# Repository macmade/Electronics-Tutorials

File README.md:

Electronics-Tutorials
=====================

### About

Various electronics test projects.

### Software

Schemas and PCB layouts are created with KiCad:  
http://www.kicad-pcb.org

#### Footprints Library

This project requires the [XS-Labs KiCad Library](https://github.com/macmade/XS-KiCad-Library) to be installed in KiCad.

### Projects

  - [Astable Multivibrator](#1)
  - [SR Latch](#2)
  - [NPN Logic Gates](#3)

Astable Multivibrator
---------------------

### Bill Of Materials

| Manufacturer            | Part No.             | Details                                                                  | Quantity |
|-------------------------|----------------------|--------------------------------------------------------------------------|----------|
| ON Semiconductor        | [BC547BTF]           | Bipolar Transistors - BJT NPN 45V 100mA HFE/450                          | 2        |
| Vishay                  | [MAL214258109E3]     | Aluminium Electrolytic Capacitors - Radial Leaded 10uF 63V 20%           | 2        |
| VCC                     | [4302H1-12V]         | Standard LEDs - Red - 12V                                                | 2        |
| Vishay                  | [CCF071K00JKE36]     | Metal Film Resistors 1/4watt 1Kohms 5%                                   | 2        |
| Vishay                  | [CCF07100KJKE36]     | Metal Film Resistors 1/4watt 100Kohms 5%                                 | 2        |
| Wurth Elektronik        | [691214110002]       | Fixed Terminal Blocks WR-TBL 300VAC 10A 2P Horizontal                    | 1        |

[BC547BTF]: https://www.mouser.ch/ProductDetail/512-BC547BTF
[MAL214258109E3]: https://www.mouser.ch/ProductDetail/594-MAL203858109E3
[4302H1-12V]: https://www.mouser.ch/ProductDetail/606-4302H1-12V
[CCF071K00JKE36]: https://www.mouser.ch/ProductDetail/71-CCF071K00JKE36
[CCF07100KJKE36]: https://www.mouser.ch/ProductDetail/71-CCF07100KJKE36
[691214110002]: https://www.mouser.ch/ProductDetail/710-691214110002

SR Latch
--------

### Bill Of Materials

| Manufacturer            | Part No.             | Details                                                                  | Quantity |
|-------------------------|----------------------|--------------------------------------------------------------------------|----------|
| ON Semiconductor        | [BC547BTF]           | Bipolar Transistors - BJT NPN 45V 100mA HFE/450                          | 4        |
| VCC                     | [4302H5-12V]         | Standard LEDs - Green - 12V                                              | 1        |
| VCC                     | [4302H1-12V]         | Standard LEDs - Red - 12V                                                | 1        |
| Vishay                  | [CCF07390RJKE36]     | Metal Film Resistors 1/4watt 390ohms 5%                                  | 2        |
| Vishay                  | [CCF071K00JKE36]     | Metal Film Resistors 1/4watt 1Kohms 5%                                   | 4        |
| Vishay                  | [CCF0710K0JKE36]     | Metal Film Resistors 1/4watt 10Kohms 5%                                  | 4        |
| Omron                   | [B3W-9010-R1R]       | Tactile Switches - Green                                                 | 1        |
| Omron                   | [B3W-9010-R1R]       | Tactile Switches - Red                                                   | 1        |
| Wurth Elektronik        | [691214110002]       | Fixed Terminal Blocks WR-TBL 300VAC 10A 2P Horizontal                    | 1        |

[BC547BTF]: https://www.mouser.ch/ProductDetail/512-BC547BTF
[4302H5-12V]: https://www.mouser.ch/ProductDetail/606-4302H5-12V
[4302H1-12V]: https://www.mouser.ch/ProductDetail/606-4302H1-12V
[CCF07390RJKE36]: https://www.mouser.ch/ProductDetail/71-CCF07390RJKE36
[CCF071K00JKE36]: https://www.mouser.ch/ProductDetail/71-CCF071K00JKE36
[CCF0710K0JKE36]: https://www.mouser.ch/ProductDetail/71-CCF0710K0JKE36
[B3W-9010-G1G]: https://www.mouser.ch/ProductDetail/653-B3W-9010-G1G
[B3W-9010-R1R]: https://www.mouser.ch/ProductDetail/653-B3W-9010-R1R
[691214110002]: https://www.mouser.ch/ProductDetail/710-691214110002

NPN Logic Gates
---------------

| Manufacturer            | Part No.             | Details                                                                  | Quantity |
|-------------------------|----------------------|--------------------------------------------------------------------------|----------|
| ON Semiconductor        | [BC547BTF]           | Bipolar Transistors - BJT NPN 45V 100mA HFE/450                          | 24       |
| VCC                     | [4302H5-12V]         | Standard LEDs - Green - 12V                                              | 6        |
| VCC                     | [4302H1-12V]         | Standard LEDs - Red - 12V                                                | 4        |
| Vishay                  | [CCF07390RJKE36]     | Metal Film Resistors 1/4watt 390ohms 5%                                  | 10       |
| Vishay                  | [CCF071K00JKE36]     | Metal Film Resistors 1/4watt 1Kohms 5%                                   | 14       |
| Vishay                  | [CCF0710K0JKE36]     | Metal Film Resistors 1/4watt 10Kohms 5%                                  | 24       |
| NKK Switches            | [M2012SA1W03]        | Toggle Switches ON-ON PC SPDT                                            | 2        |
| Wurth Elektronik        | [691214110002]       | Fixed Terminal Blocks WR-TBL 300VAC 10A 2P Horizontal                    | 1        |

[BC547BTF]: https://www.mouser.ch/ProductDetail/512-BC547BTF
[4302H5-12V]: https://www.mouser.ch/ProductDetail/606-4302H5-12V
[4302H1-12V]: https://www.mouser.ch/ProductDetail/606-4302H1-12V
[CCF07390RJKE36]: https://www.mouser.ch/ProductDetail/71-CCF07390RJKE36
[CCF071K00JKE36]: https://www.mouser.ch/ProductDetail/71-CCF071K00JKE36
[CCF0710K0JKE36]: https://www.mouser.ch/ProductDetail/71-CCF0710K0JKE36
[M2012SA1W03]: https://www.mouser.ch/ProductDetail/633-M2012A03
[691214110002]: https://www.mouser.ch/ProductDetail/710-691214110002

License
-------

All project files are released under the terms of the CERN Open Hardware License - CERN OHL v.1.2.

Repository Infos
----------------

    Owner:          Jean-David Gadina - XS-Labs
    Web:            www.xs-labs.com
    Blog:           www.noxeos.com
    Twitter:        @macmade
    GitHub:         github.com/macmade
    LinkedIn:       ch.linkedin.com/in/macmade/
    StackOverflow:  stackoverflow.com/users/182676/macmade

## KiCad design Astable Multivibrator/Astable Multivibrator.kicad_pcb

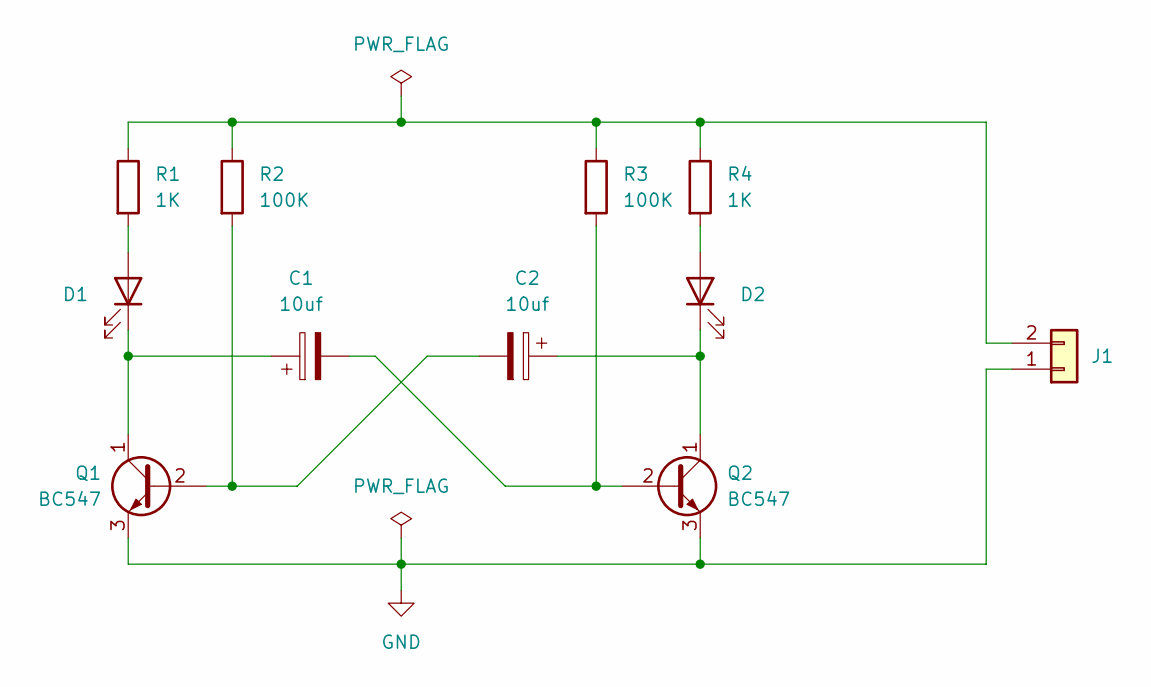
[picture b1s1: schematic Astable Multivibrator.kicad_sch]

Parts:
C1, C2: 10uf; Capacitor-Vishay-142-RHS-5x11x2mm
D1, D2: LED; LED-T1-34-5mm
J1: Conn_01x02; Connector-Wurth-Terminal-Block-2P-3.5mm-691214110002
Q1, Q2: BC547; Transistor-NPN-TO-92-Line-Spacing-Lead-Form
R1, R4: 1K; Resistor-Vishay-CCF07
R2, R3: 100K; Resistor-Vishay-CCF07

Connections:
GND: J1.1, Q1.3 (E), Q2.3 (E)
unnamed: D1.2 (A), R1.2
unnamed: C1.1, D1.1 (K), Q1.1 (C)
unnamed: D2.2 (A), R4.2
unnamed: C2.1, D2.1 (K), Q2.1 (C)
unnamed: J1.2, R1.1, R2.1, R3.1, R4.1
unnamed: C2.2, Q1.2 (B), R2.2
unnamed: C1.2, Q2.2 (B), R3.2

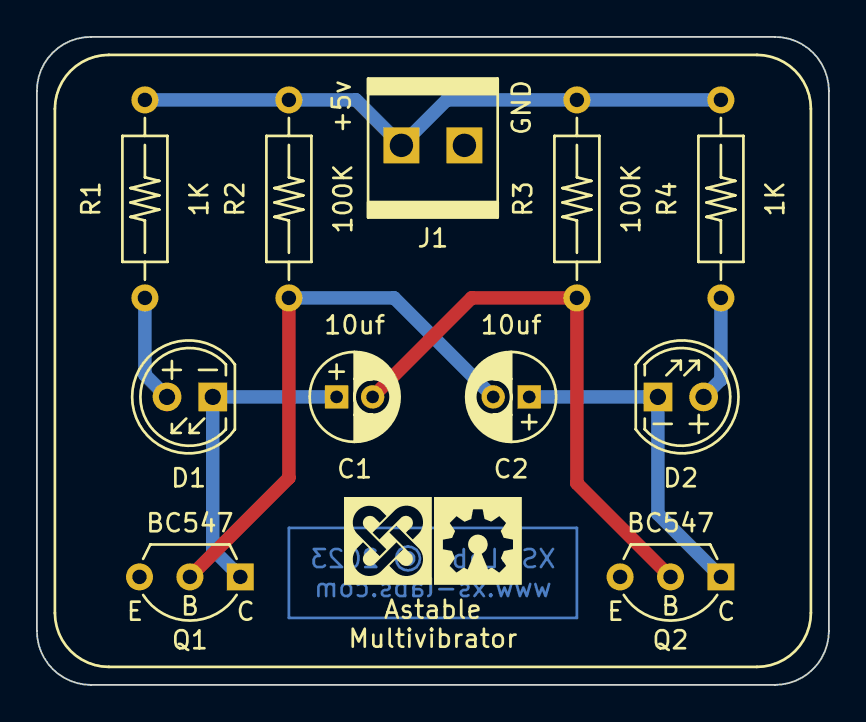
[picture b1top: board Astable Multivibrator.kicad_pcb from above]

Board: 2 copper layers, 44.0 x 36.0 mm, 11 parts (0 on the bottom side), 8 nets.

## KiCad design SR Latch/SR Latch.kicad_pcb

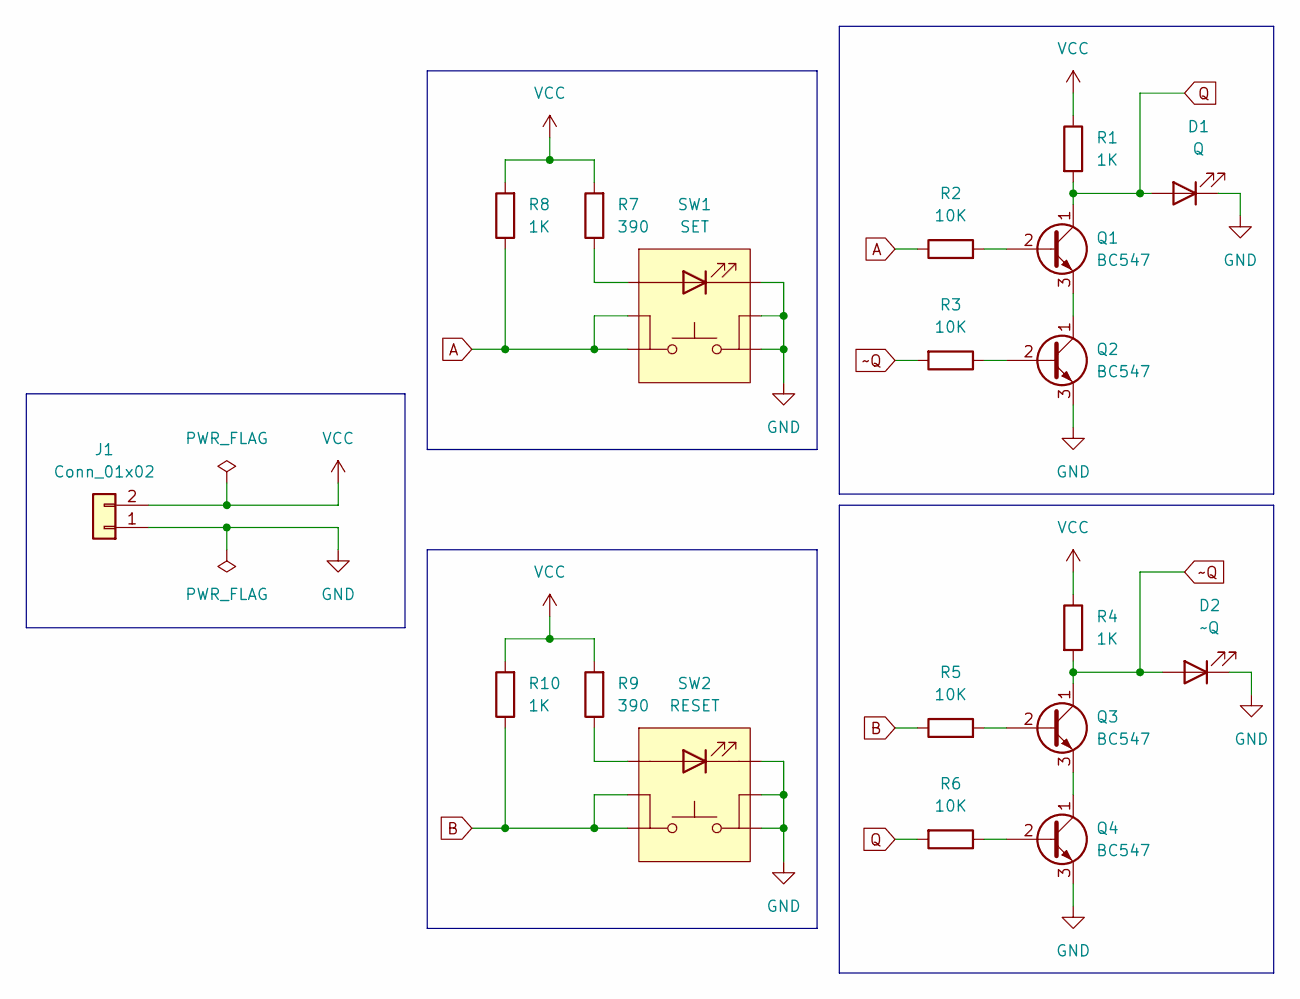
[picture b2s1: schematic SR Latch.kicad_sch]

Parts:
D1: Q; LED-T1-34-5mm
D2: ~Q; LED-T1-34-5mm
J1: Conn_01x02; Connector-Wurth-Terminal-Block-2P-3.5mm-691214110002
Q1, Q2, Q3, Q4: BC547; Package-TO-92-Line-Spacing-Lead-Form
R1, R4, R8, R10: 1K; Resistor-Vishay-CCF07
R2, R3, R5, R6: 10K; Resistor-Vishay-CCF07
R7, R9: 390; Resistor-Vishay-CCF07
SW1: SET; Tactile-Omron-B3W-900X-X1X
SW2: RESET; Tactile-Omron-B3W-900X-X1X

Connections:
A: R2.1, R8.1, SW1.3, SW1.4
B: R5.1, R10.1, SW2.3, SW2.4
GND: D1.1 (K), D2.1 (K), J1.1, Q2.3 (E), Q4.3 (E), SW1.1, SW1.2, SW1.5 (K), SW2.1, SW2.2, SW2.5 (K)
unnamed: Q1.2 (B), R2.2
unnamed: Q1.3 (E), Q2.1 (C)
unnamed: Q2.2 (B), R3.1
unnamed: Q3.2 (B), R5.2
unnamed: Q3.3 (E), Q4.1 (C)
unnamed: Q4.2 (B), R6.1
unnamed: R7.1, SW1.6 (A)
unnamed: R9.1, SW2.6 (A)
Q: D1.2 (A), Q1.1 (C), R1.2, R6.2
VCC: J1.2, R1.1, R4.1, R7.2, R8.2, R9.2, R10.2
~Q: D2.2 (A), Q3.1 (C), R3.2, R4.2

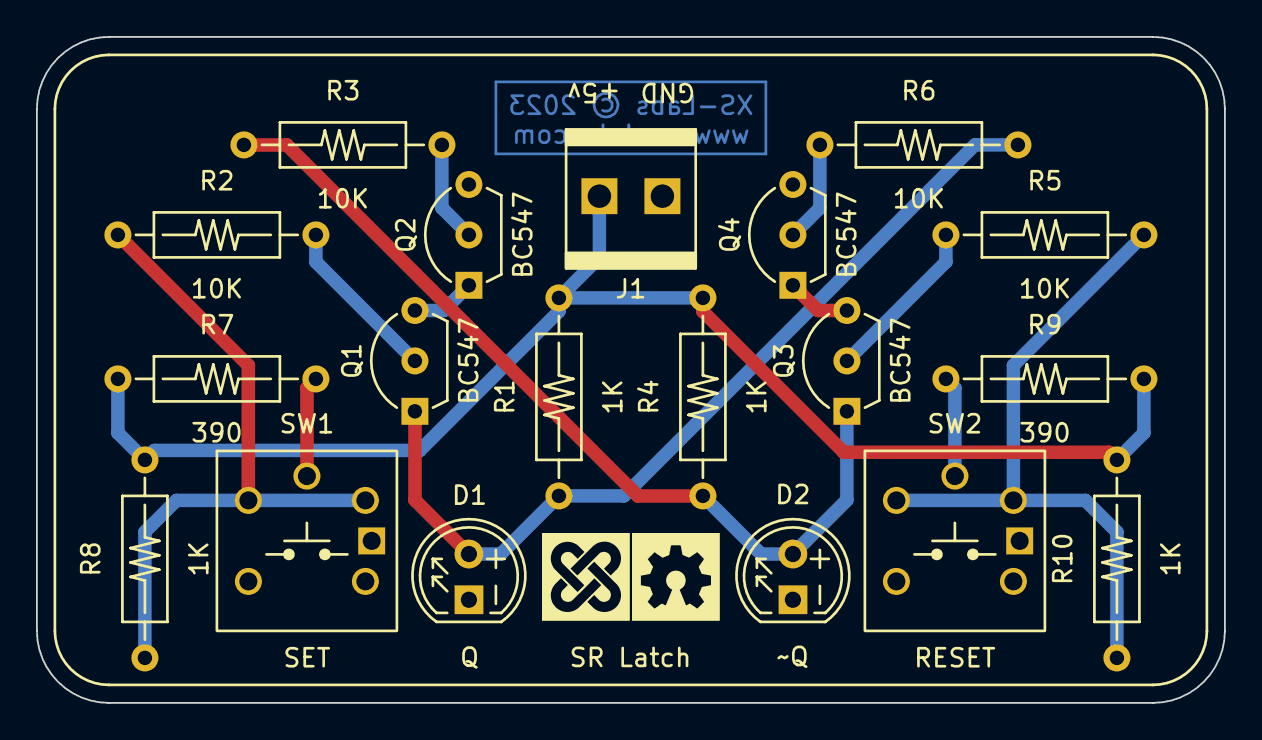
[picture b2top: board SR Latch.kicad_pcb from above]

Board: 2 copper layers, 66.0 x 37.0 mm, 19 parts (0 on the bottom side), 14 nets.

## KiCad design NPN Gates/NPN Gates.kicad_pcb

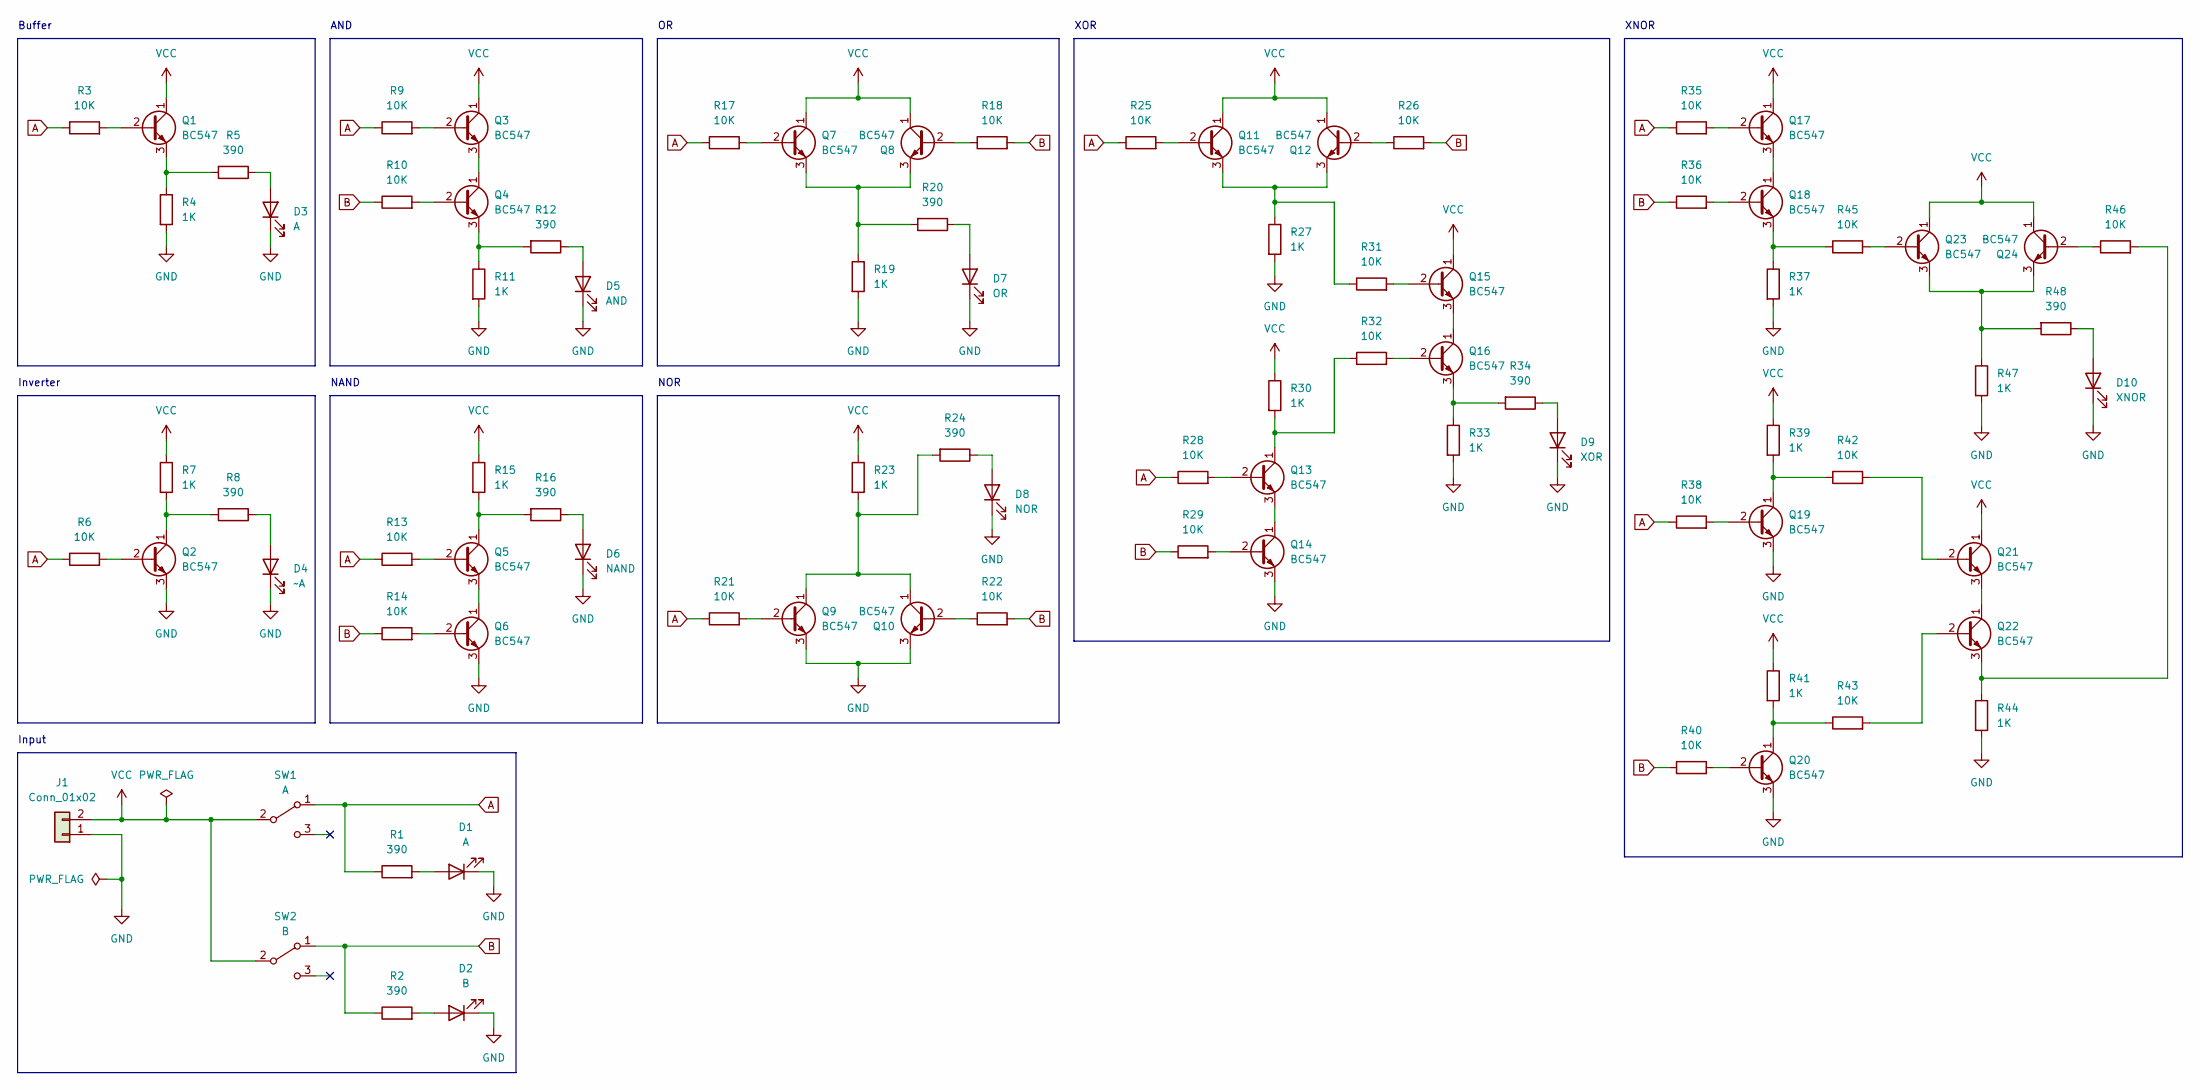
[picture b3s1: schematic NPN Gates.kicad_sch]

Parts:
D1, D3: A; LED-T1-34-5mm
D2: B; LED-T1-34-5mm
D4: ~A; LED-T1-34-5mm
D5: AND; LED-T1-34-5mm
D6: NAND; LED-T1-34-5mm
D7: OR; LED-T1-34-5mm
D8: NOR; LED-T1-34-5mm
D9: XOR; LED-T1-34-5mm
D10: XNOR; LED-T1-34-5mm
J1: Conn_01x02; Connector-Wurth-Terminal-Block-2P-3.5mm-691214110002
Q1, Q2, Q3, Q4, Q5, Q6, Q7, Q8, Q9, Q10, Q11, Q12, Q13, Q14, Q15, Q16, Q17, Q18, Q19, Q20, Q21, Q22, Q23, Q24: BC547; Transistor-NPN-TO-92-Line-Spacing-Lead-Form
R1, R2, R5, R8, R12, R16, R20, R24, R34, R48: 390; Resistor-Vishay-CCF07
R3, R6, R9, R10, R13, R14, R17, R18, R21, R22, R25, R26, R28, R29, R31, R32, R35, R36, R38, R40, R42, R43, R45, R46: 10K; Resistor-Vishay-CCF07
R4, R7, R11, R15, R19, R23, R27, R30, R33, R37, R39, R41, R44, R47: 1K; Resistor-Vishay-CCF07
SW1: A; Switch-SPDT-NKK-Series-M
SW2: B; Switch-SPDT-NKK-Series-M

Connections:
A: R1.1, R3.1, R6.1, R9.1, R13.1, R17.1, R21.1, R25.1, R28.1, R35.1, R38.1, SW1.1 (A)
B: R2.1, R10.1, R14.1, R18.2, R22.2, R26.2, R29.1, R36.1, R40.1, SW2.1 (A)
GND: D1.1 (K), D2.1 (K), D3.1 (K), D4.1 (K), D5.1 (K), D6.1 (K), D7.1 (K), D8.1 (K), D9.1 (K), D10.1 (K), J1.1, Q2.3 (E), Q6.3 (E), Q9.3 (E), Q10.3 (E), Q14.3 (E), Q19.3 (E), Q20.3 (E), R4.2, R11.2, R19.2, R27.2, R33.2, R37.2, R44.2, R47.2
unnamed: D1.2 (A), R1.2
unnamed: D2.2 (A), R2.2
unnamed: D3.2 (A), R5.1
unnamed: D4.2 (A), R8.1
unnamed: D5.2 (A), R12.1
unnamed: D6.2 (A), R16.1
unnamed: D7.2 (A), R20.1
unnamed: D8.2 (A), R24.1
unnamed: D9.2 (A), R34.1
unnamed: D10.2 (A), R48.1
unnamed: Q1.2 (B), R3.2
unnamed: Q1.3 (E), R4.1, R5.2
unnamed: Q2.2 (B), R6.2
unnamed: Q2.1 (C), R7.2, R8.2
unnamed: Q3.2 (B), R9.2
unnamed: Q3.3 (E), Q4.1 (C)
unnamed: Q4.2 (B), R10.2
unnamed: Q4.3 (E), R11.1, R12.2
unnamed: Q5.2 (B), R13.2
unnamed: Q5.1 (C), R15.2, R16.2
unnamed: Q5.3 (E), Q6.1 (C)
unnamed: Q6.2 (B), R14.2
unnamed: Q7.2 (B), R17.2
unnamed: Q7.3 (E), Q8.3 (E), R19.1, R20.2
unnamed: Q8.2 (B), R18.1
unnamed: Q9.2 (B), R21.2
unnamed: Q10.2 (B), R22.1
unnamed: Q9.1 (C), Q10.1 (C), R23.2, R24.2
unnamed: Q11.2 (B), R25.2
unnamed: Q11.3 (E), Q12.3 (E), R27.1, R31.1
unnamed: Q12.2 (B), R26.1
unnamed: Q13.2 (B), R28.2
unnamed: Q13.1 (C), R30.2, R32.1
unnamed: Q13.3 (E), Q14.1 (C)
unnamed: Q14.2 (B), R29.2
unnamed: Q15.2 (B), R31.2
unnamed: Q15.3 (E), Q16.1 (C)
unnamed: Q16.2 (B), R32.2
unnamed: Q16.3 (E), R33.1, R34.2
unnamed: Q17.2 (B), R35.2
unnamed: Q17.3 (E), Q18.1 (C)
unnamed: Q18.2 (B), R36.2
unnamed: Q18.3 (E), R37.1, R45.1
unnamed: Q19.2 (B), R38.2
unnamed: Q19.1 (C), R39.2, R42.1
unnamed: Q20.2 (B), R40.2
unnamed: Q20.1 (C), R41.2, R43.1
unnamed: Q21.2 (B), R42.2
unnamed: Q21.3 (E), Q22.1 (C)
unnamed: Q22.2 (B), R43.2
unnamed: Q22.3 (E), R44.1, R46.2
unnamed: Q23.2 (B), R45.2
unnamed: Q23.3 (E), Q24.3 (E), R47.1, R48.2
unnamed: Q24.2 (B), R46.1
VCC: J1.2, Q1.1 (C), Q3.1 (C), Q7.1 (C), Q8.1 (C), Q11.1 (C), Q12.1 (C), Q15.1 (C), Q17.1 (C), Q21.1 (C), Q23.1 (C), Q24.1 (C), R7.1, R15.1, R23.1, R30.1, R39.1, R41.1, SW1.2 (B), SW2.2 (B)

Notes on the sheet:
XNOR
Buffer
XOR
NAND
Inverter
AND
NOR
Input

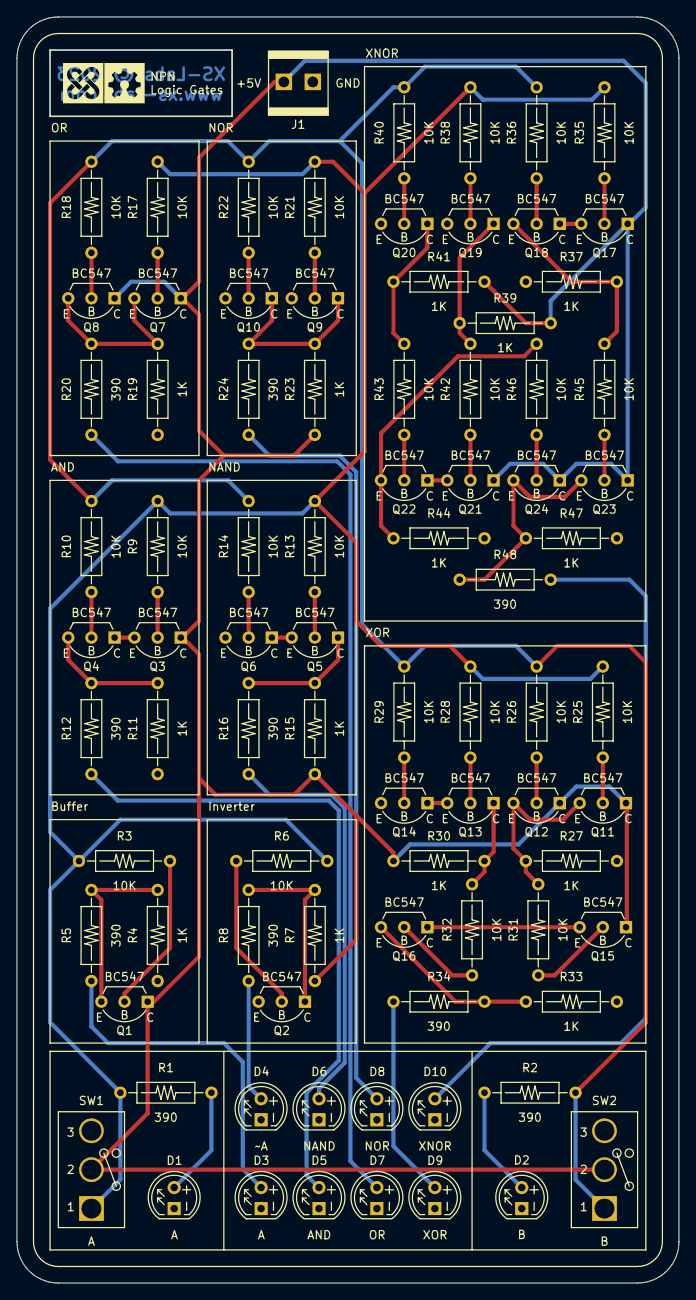
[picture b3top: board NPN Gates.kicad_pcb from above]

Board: 2 copper layers, 80.0 x 153.0 mm, 85 parts (0 on the bottom side), 58 nets.

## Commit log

2023-10-27 chore: README
2023-10-27 chore: .gitignore
2023-10-27 chore: COC
2023-10-27 chore: License
2023-10-27 chore: GitHub Sponsors
2023-10-28 feat: Astable Multivibrator
2023-10-28 feat: Replaced the pin header by a terminal block.
2023-10-30 chore: Footprints update
2023-10-30 feat: SR Latch
2023-10-30 fix(SR Latch): Updated resistor values
2023-11-01 fix: DRC fixes
2023-11-01 feat: NPN Gates
2023-11-02 fix: Fixed the SR Latch project (Omron tactile switches)
2023-11-03 chore: Astable Multivibrator BOM + Assets update
2023-11-03 chore: Using D for LEDs instead of DS
2023-11-03 chore: SL Latch Assets + BOM
2023-11-03 chore: NPN Gates Assets + BOM
2023-11-13 fix: SR Latch - Fixed the SET/RESET labels
2023-12-01 fix: Fixed the NPN Gates project with a new design
2023-12-01 chore: BOM update

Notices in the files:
Astable Multivibrator/Astable Multivibrator.kicad_pcb:
XS-Labs © 2023
README.md:
License: ohl
